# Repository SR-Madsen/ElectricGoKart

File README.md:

# Electric Go-Kart
Repository for 1st semester project of the Master in Electronics at the University of Southern Denmark relating to controlling a Permanent-Magnet Synchronous Motor for an electric go-kart.

## Purpose
The repository contains KiCad files and programming files from Vivado and the Xilinx SDK used for designing a three-phase inverter with a Zybo Zynq-7010 processing unit as core. As described within the repository, a system already exists that the inverter must fit within.

## Overview

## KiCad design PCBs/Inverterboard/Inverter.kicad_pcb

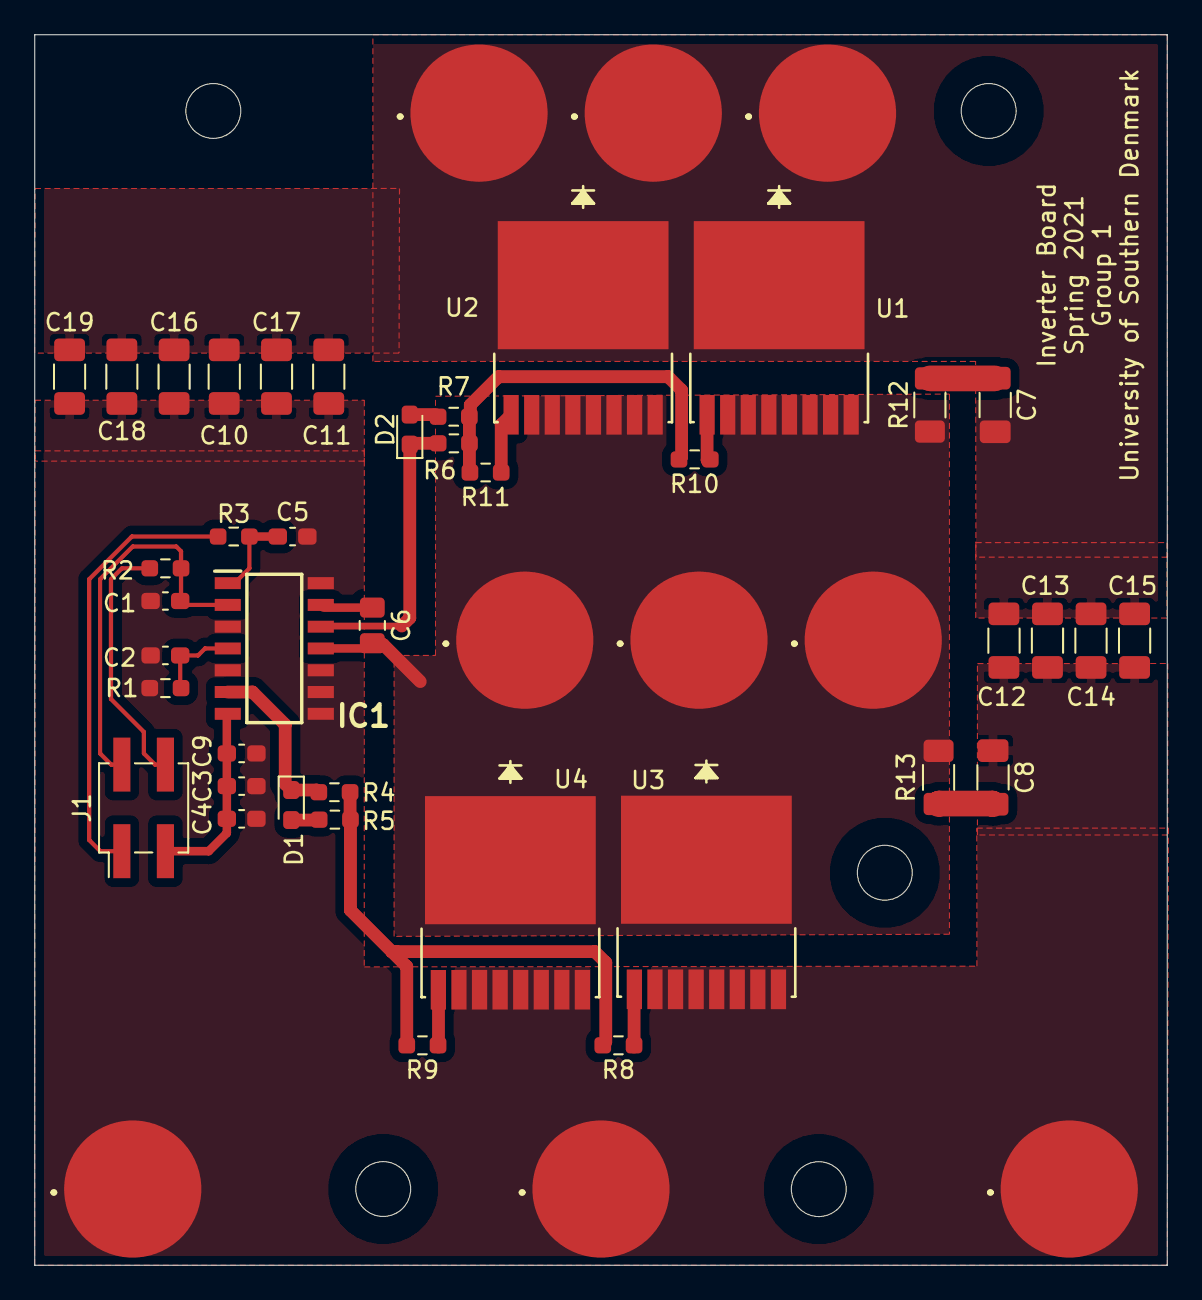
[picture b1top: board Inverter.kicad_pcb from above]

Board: 2 copper layers, 66.0 x 71.8 mm, 49 parts (0 on the bottom side), 22 nets.

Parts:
C1, C9: 1n; C_0603_1608Metric_Pad1.08x0.95mm_HandSolder
C2, C4: 100n; C_0603_1608Metric_Pad1.08x0.95mm_HandSolder
C3: 1µ; C_0603_1608Metric_Pad1.08x0.95mm_HandSolder
C5: 100p; C_0603_1608Metric_Pad1.08x0.95mm_HandSolder
C6: 1µ; C_0805_2012Metric_Pad1.18x1.45mm_HandSolder
C7, C8: 33n; C_1206_3216Metric_Pad1.33x1.80mm_HandSolder
C10, C11, C16, C17, C18, C19: 4.7µ; C_1206_3216Metric_Pad1.33x1.80mm_HandSolder
C12: 1µ; C_1206_3216Metric_Pad1.33x1.80mm_HandSolder
C13: 100n; C_1206_3216Metric_Pad1.33x1.80mm_HandSolder
C14: 10n; C_1206_3216Metric_Pad1.33x1.80mm_HandSolder
C15: 1n; C_1206_3216Metric_Pad1.33x1.80mm_HandSolder
D1, D2: D; D_0603_1608Metric_Pad1.05x0.95mm_HandSolder
IC1: L6494LDTR
J1: Conn_02x02_Odd_Even; PinHeader_2x02_P2.54mm_Vertical_SMD
R1: 1k; R_0603_1608Metric_Pad0.98x0.95mm_HandSolder
R2: 10k; R_0603_1608Metric_Pad0.98x0.95mm_HandSolder
R3: 2k; R_0603_1608Metric_Pad0.98x0.95mm_HandSolder
R4, R6: 22; R_0603_1608Metric_Pad0.98x0.95mm_HandSolder
R5, R7: 0; R_0603_1608Metric_Pad0.98x0.95mm_HandSolder
R8, R9, R10, R11: 3.3; R_0603_1608Metric_Pad0.98x0.95mm_HandSolder
R12, R13: 1; R_1206_3216Metric_Pad1.30x1.75mm_HandSolder
U1, U2, U3, U4: PG-HSOF-8-1_INF; IPT015N10N5ATMA1
U**: 7466203R
U**#2, U**#3, U**#4, U**#5, U**#6, U**#7, U**#8, U**#9: 7466203R

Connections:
+5V: J1.4, R2.1
+12V: C3.1, C4.2, C9.1, IC1.7, J1.3
+BATT: C7.2, C10.1, C11.1, C12.1, C13.1, C14.1, C15.1, C16.1, C17.1, C18.1, C19.1, U1.9, U2.9, U**#7.1, U**#8.1, U**#9.1
Enable: C1.1, IC1.2, J1.2, R2.2
GND: C1.2, C2.2, C3.2, C4.1, C5.2, C8.1, C9.2, C10.2, C11.2, C12.2, C13.2, C14.2, C15.2, C16.2, C17.2, C18.2, C19.2, IC1.3, IC1.5, IC1.8, IC1.9, IC1.10, IC1.14, R1.2, U3.2, U3.3, U3.4, U3.5, U3.6, U3.7, U3.8, U4.2, U4.3, U4.4, U4.5, U4.6, U4.7, U4.8, U**.1, U**#2.1, U**#3.1
unnamed: C2.1, IC1.4, R1.1
unnamed: C5.1, IC1.1, R3.1
unnamed: C6.1, IC1.13
unnamed: C7.1, R12.2
unnamed: C8.2, R13.1
unnamed: D1.1, IC1.6, R4.2
unnamed: D1.2, R5.2
unnamed: D2.1, IC1.12, R6.2
unnamed: D2.2, R7.2
unnamed: R4.1, R5.1, R8.2, R9.2
unnamed: R8.1, U3.1
unnamed: R9.1, U4.1
unnamed: R10.1, U1.1
unnamed: R6.1, R7.1, R10.2, R11.2
unnamed: R11.1, U2.1
PHASE: C6.2, IC1.11, R12.1, R13.2, U1.2, U1.3, U1.4, U1.5, U1.6, U1.7, U1.8, U2.2, U2.3, U2.4, U2.5, U2.6, U2.7, U2.8, U3.9, U4.9, U**#4.1, U**#5.1, U**#6.1
PWM: J1.1, R3.2

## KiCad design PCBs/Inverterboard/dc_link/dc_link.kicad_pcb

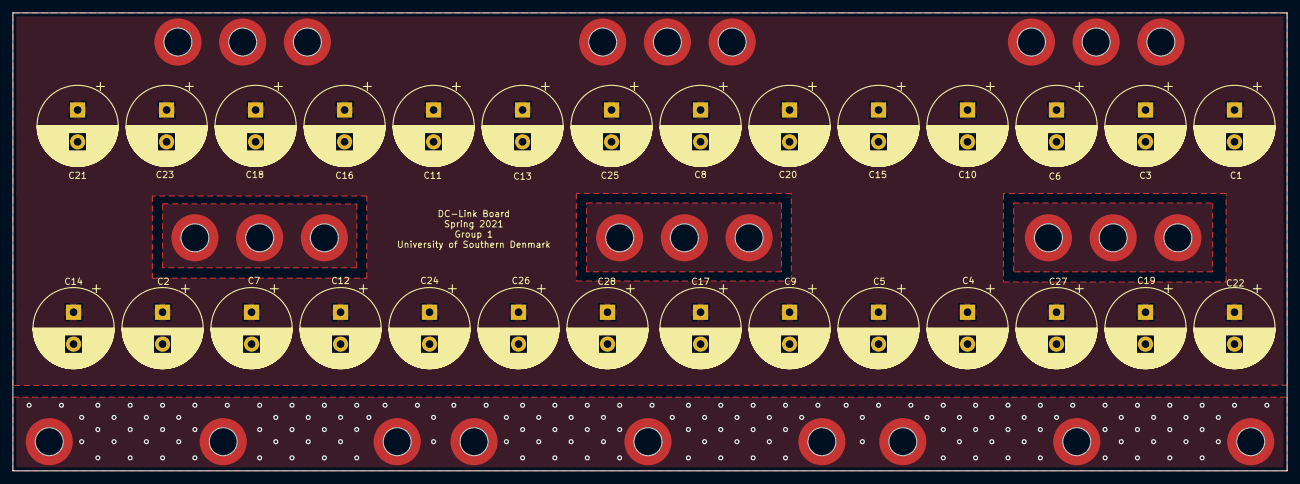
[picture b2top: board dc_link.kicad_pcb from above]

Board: 2 copper layers, 200.0 x 71.9 mm, 28 parts (0 on the bottom side), 2 nets.

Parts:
C1, C2, C3, C4, C5, C6, C7, C8, C9, C10, C11, C12, C13, C14, C15, C16, C17, C18, C19, C20, C21, C22, C23, C24, C25, C26, C27, C28: CP; CP_Radial_D12.5mm_P5.00mm

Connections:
+BATT: C1.1, C2.1, C3.1, C4.1, C5.1, C6.1, C7.1, C8.1, C9.1, C10.1, C11.1, C12.1, C13.1, C14.1, C15.1, C16.1, C17.1, C18.1, C19.1, C20.1, C21.1, C22.1, C23.1, C24.1, C25.1, C26.1, C27.1, C28.1
GND: C1.2, C2.2, C3.2, C4.2, C5.2, C6.2, C7.2, C8.2, C9.2, C10.2, C11.2, C12.2, C13.2, C14.2, C15.2, C16.2, C17.2, C18.2, C19.2, C20.2, C21.2, C22.2, C23.2, C24.2, C25.2, C26.2, C27.2, C28.2

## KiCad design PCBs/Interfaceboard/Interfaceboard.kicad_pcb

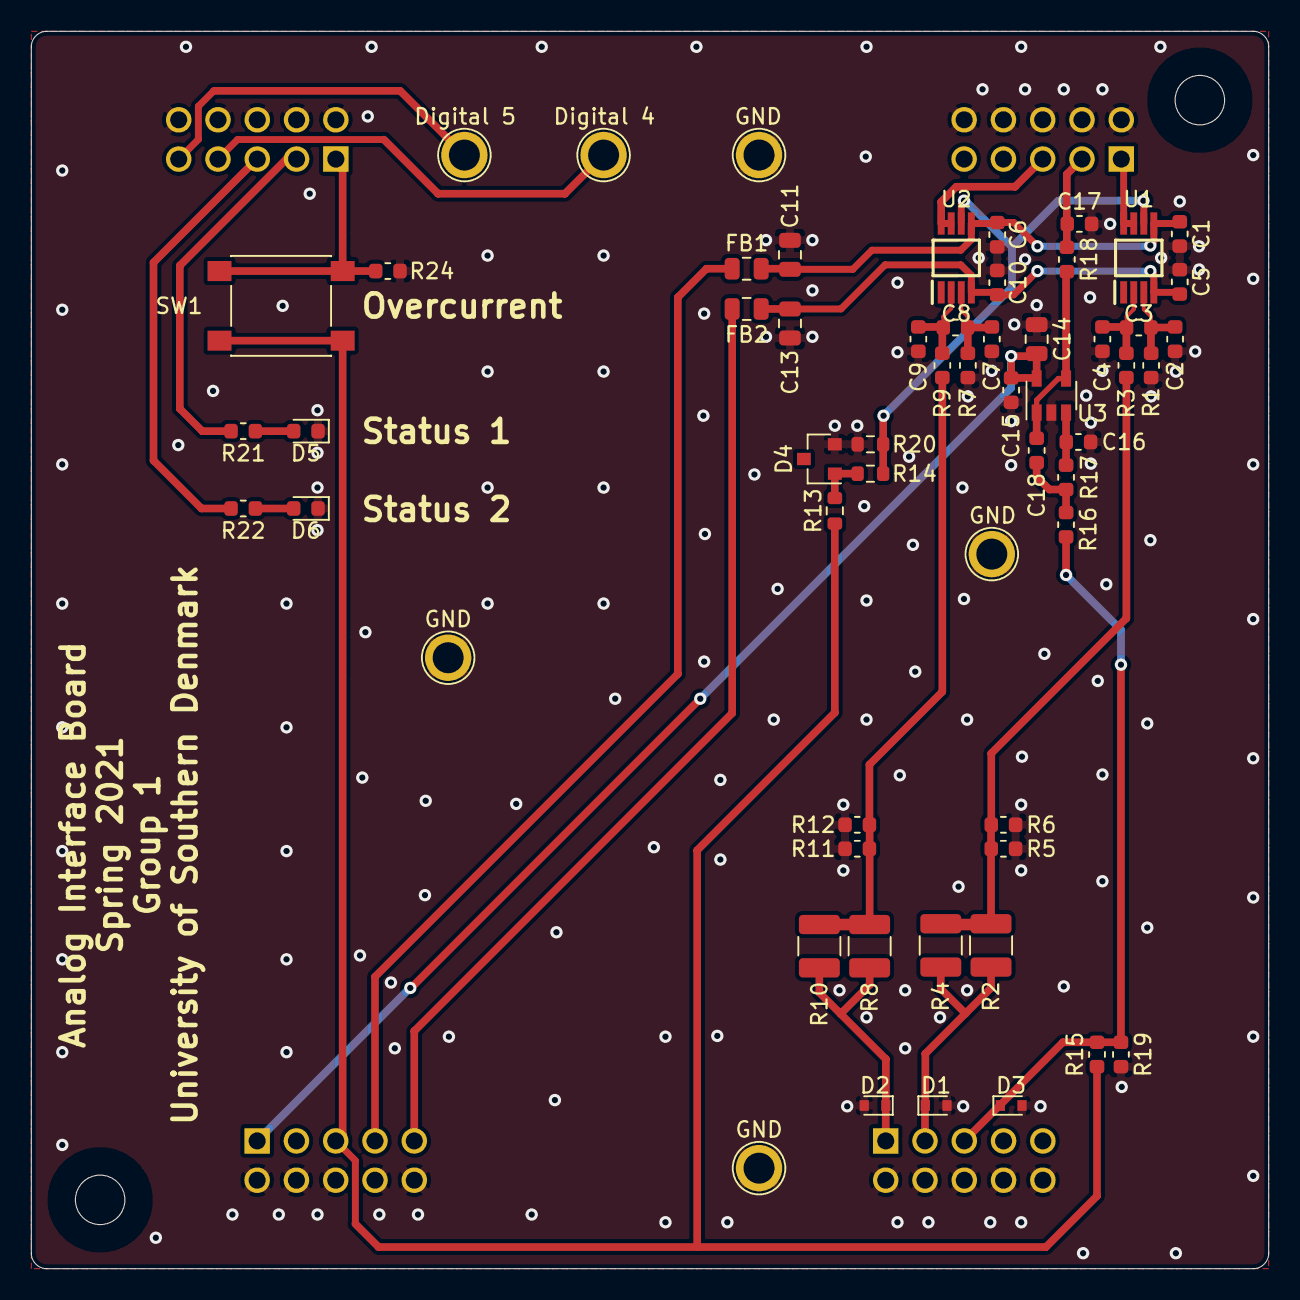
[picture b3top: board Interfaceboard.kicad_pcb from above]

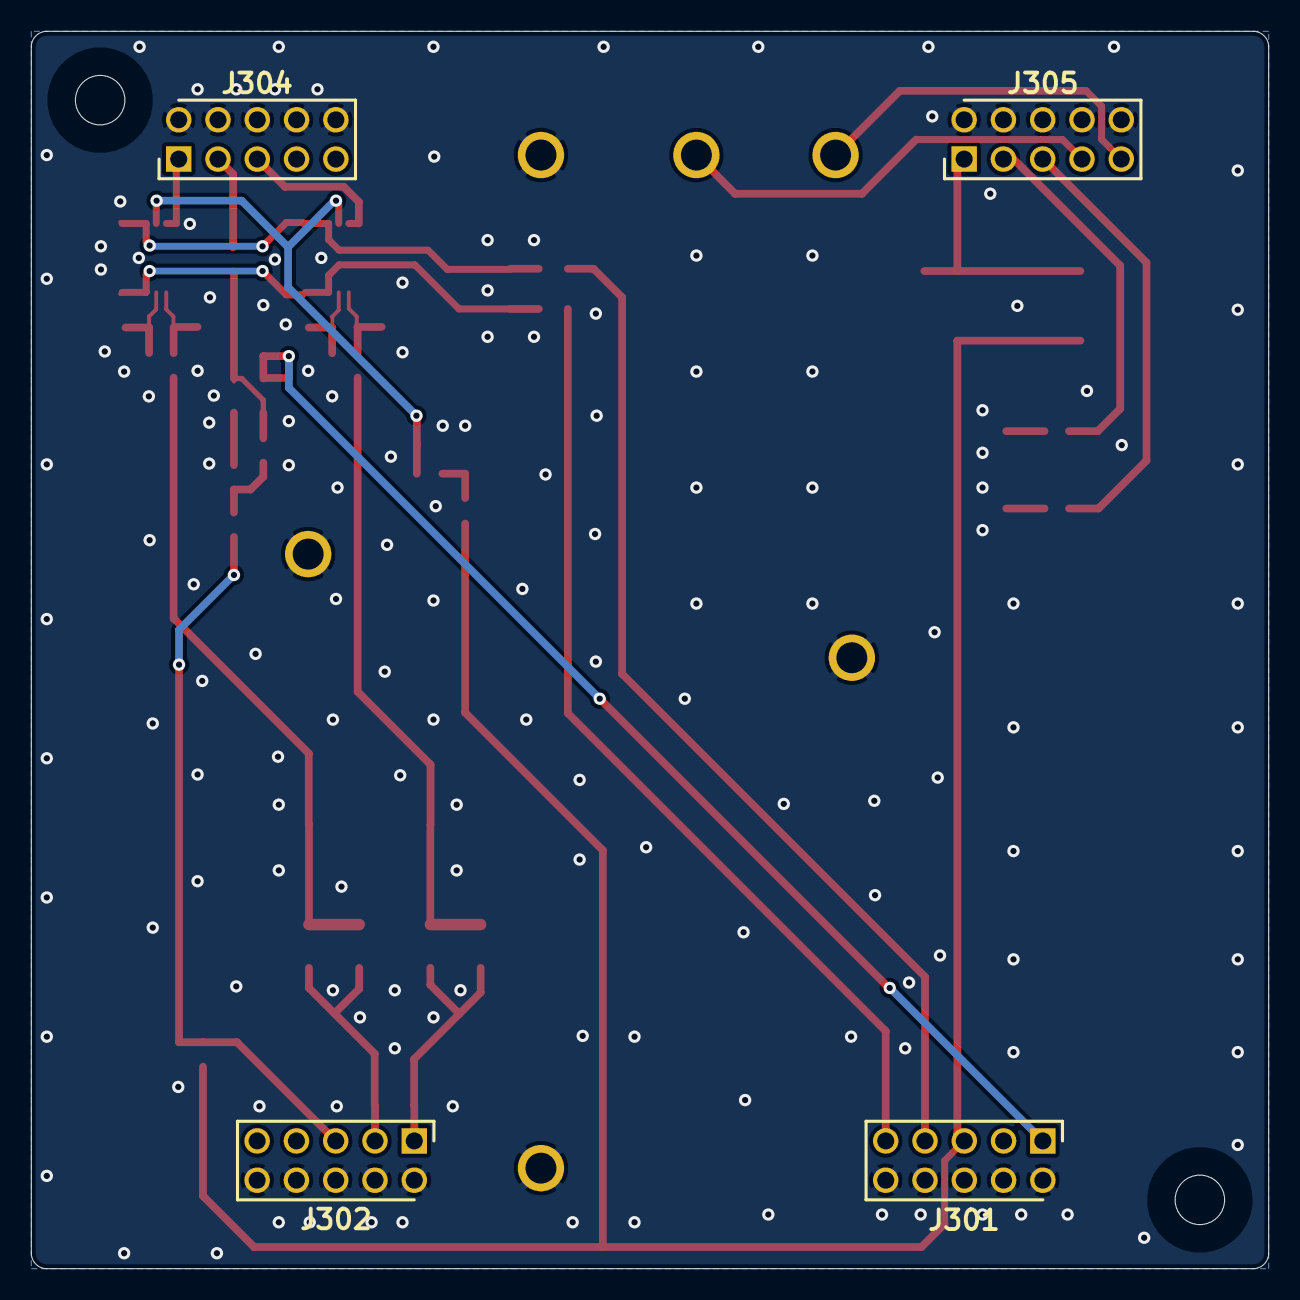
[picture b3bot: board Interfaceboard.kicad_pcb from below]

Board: 2 copper layers, 80.0 x 80.0 mm, 64 parts (4 on the bottom side), 31 nets.

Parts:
C1, C5, C6, C10, C15: 100n; C_0603_1608Metric
C2, C4, C7, C9: 100p; C_0603_1608Metric
C3, C8: 1n; C_0603_1608Metric
C11, C13, C14: 10µ; C_0805_2012Metric
C16: 30n; C_0603_1608Metric
C17: 33n; C_0603_1608Metric
C18: 56n; C_0603_1608Metric
D1, D2: 5 V; D_SOD-523
D3: 3.3 V; D_SOD-523
D4: LM4041CFTA; LM4041
D5: 150060SS75000; LED_0603_1608Metric
D6: 150060VS75000; LED_0603_1608Metric
FB1, FB2: 400 mA, 1k5; L_0805_2012Metric
H1, H2: M3 Mount; MountingHole_3.2mm_M3
J301, J302, J304, J305: TSW-105-07-T-D
R1, R3, R7, R9: 20k; R_0603_1608Metric
R2, R8: 54.9; R_1210_3225Metric
R4, R10: 56; R_1210_3225Metric
R5, R11: 3.09; R_0603_1608Metric
R6, R12: DNP; R_0603_1608Metric
R13: 5.1k; R_0603_1608Metric
R14: 1.43k; R_0603_1608Metric
R15: 11.5k; R_0603_1608Metric
R16, R17: 7.5k; R_0603_1608Metric
R18: 147; R_0603_1608Metric
R19, R24: 10k; R_0603_1608Metric
R20: 1k; R_0603_1608Metric
R21, R22: 270; R_0603_1608Metric
SW1: PTS645; SW_SPST_PTS645
TP4, TP5, TP6, TP7, TP8, TP9: TestPoint; TestPoint_Plated_Hole_D2.0mm
U1, U2: AD8420ARMZ
U3: MCP6L01x-xOT; SOT-23-5

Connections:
+3V3_Ref: J301.5, R13.2, R15.1, SW1.1
+5V: C14.1, C15.1, J301.1, U3.5
+15V: FB1.1, J301.7
-15V: FB2.2, J301.9
/Buttons/Dig1: J305.1, R24.1, SW1.2
/Buttons/Dig2: J305.3, R21.2
/Buttons/Dig3: J305.5, R22.2
/Buttons/Dig4: J305.7, TP8.1
/Buttons/Dig5: J305.9, TP9.1
/Connectors/ADC1: J304.1, U1.7, U1.8
/Connectors/ADC3: C17.1, J304.3, R18.1
/Connectors/ADC4: J304.5, U2.7, U2.8
/Connectors/Torque_Meas: D3.1, J302.5, R15.2, R16.2, R19.1
/Currents/0V5: R14.1, R20.2, U1.6, U2.6
/Currents/+15V_Filt: C1.1, C6.1, C11.1, FB1.2, U1.5, U2.5
/Currents/-15V_Filt: C5.1, C10.1, C13.2, FB2.1, U1.4, U2.4
/Currents/Phase1_In: D2.1, J302.1, R8.2, R10.2
/Currents/Phase2_In: D1.1, J302.3, R2.2, R4.2
GND: C1.2, C2.1, C4.2, C5.2, C6.2, C7.1, C9.2, C10.2, C11.2, C13.1, C14.2, C15.2, C16.2, C17.2, D1.2, D2.2, D3.2, D4.2, D5.1, D6.1, J301.2, J301.4, J301.6, J301.8, J301.10, J302.2, J302.4, J302.6, J302.8, J302.10, J304.2, J304.4, J304.6, J304.8, J304.10, J305.2, J305.4, J305.6, J305.8, J305.10, R1.2, R5.1, R6.1, R7.2, R11.1, R12.1, R19.2, R20.1, R24.2, TP4.1, TP5.1, TP6.1, TP7.1, U3.2
unnamed: C2.2, C3.1, R1.1, U1.3
unnamed: C3.2, C4.1, R3.1, U1.2
unnamed: C7.2, C8.1, R7.1, U2.3
unnamed: C8.2, C9.1, R9.1, U2.2
unnamed: C16.1, R17.1, U3.3
unnamed: C18.1, R18.2, U3.1, U3.4
unnamed: C18.2, R16.1, R17.2
unnamed: D4.1, R13.1, R14.2
unnamed: D5.2, R21.1
unnamed: D6.2, R22.1
unnamed: R2.1, R3.2, R4.1, R5.2, R6.2
unnamed: R8.1, R9.2, R10.1, R11.2, R12.2

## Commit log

2021-02-16 Initial commit of datasheets, KiCad project, and overview.
2021-02-17 Added newest datasheets Rakesh put up. Added some links for software design. Minor changes to draw.io file.
2021-02-18 Added KiCad Libraries for this project. Added 35 pin connector to schematic.
2021-02-19 Split into two PCBs, made sub-sheets for most. Added connectors and comments.
2021-02-20 Added multiple connectors, still lacking a few. Started work on measurement circuits for interface board.
2021-02-23 Added most circuits from Interface schematic provided by Rakesh. Lacks a few connectors, transistors, and optocouplers. Needs connections for Zybo. Awaiting feedback from meeting with Rakesh.
2021-02-23 Added Interface Board schematics
    * Added KiCad Libraries for this project. Added 35 pin connector to schematic.
    * Split into two PCBs, made sub-sheets for most. Added connectors and comments.
    * Added multiple connectors, still lacking a few. Started work on measurement circuits for interface board.
    * Added most circuits from Interface schematic provided by Rakesh. Lacks a few connectors, transistors, and optocouplers. Needs connections for Zybo. Awaiting feedback from meeting with Rakesh.
2021-03-04 Removed interface board, added analog interface board.
2021-03-08 Added analog board hierarchial sheets. Started work on connectors, supply, and in amp for phase current measurements.
2021-03-10 Finished schematics for analog interface board. Ready for review and then PCB design.
2021-03-13 Added test points and final associated footprints. Made outline for PCB.
2021-03-15 Made changes to resistor sizes and footprints. Placed switches on PCB, ready for the rest.
2021-03-15 Minor changes to schematics, removed test points, placed a few components on PCB.
2021-03-16 Removed some buttons and added LEDs. Finished placing the components on the PCB.
2021-03-16 Minor cosmetic and performance changes. PCB basically finished, needs more eyes for review.
2021-03-17 Changed M2 to M3 hole. Vias are free.
2021-03-17 Swapped some ADC channels for the signals to ensure that simultaneous conversion is possible.
2021-03-22 Merge of 'Analog Board' into main (#2)
    * Added analog board schematics and finished PCB.
    * Added a few documentation files.
2021-03-23 Added Vivado project and PWM Generator + Encoder driver IPs. Encoder driver still unfinished.
2021-03-24 Fully-tested and functional PWM IP added. Encoder module still needs simulation and further polishing.
2021-03-25 Tested and fixed Encoder driver, added both IPs to main project.
2021-03-25 Made final changes to PWM generator and Encoder driver IPs.
2021-03-26 Made final fixes to IP cores, ran implementation and bitstream of module. Added GPIO IPs and assigned pins.
2021-03-29 Fixed asynchronous reset error for IPs and optimized a bit. Now fully functional.
2021-04-03 Merge of VHDL Modules (#3)
    * Added Vivado project.
    * Created PWM Generator and Encoder Driver IPs, which along with XADC, PS, and GPIO are used in the block diagram.
    * Assigned all pins and created constraints file for timing, bitstream generated.
2021-04-03 Added progress for inverterboard and DC-link by the Jackobs. Merged libraries, added 3D models for swag factor.
2021-04-04 Added and made changes to software overview. Added PS Interrupt from XADC.
2021-04-06 Merged PCB with changes from Jakob. Added FOC overview.
2021-04-06 Connected MOSFET sources
2021-04-06 Changed mini-fits to pin headers
2021-04-08 Added mini-fit to enable and pwm signals
2021-04-13 Changed ceramic DC-link cap footprint size
2021-04-13 Made minor changes to PCB to accommodate review feedback.
2021-04-16 Last fixes after PCB review
2021-04-16 Created gerber files
2021-04-16 Something that apparently didn't get pushed before
2021-04-16 Correct gerber
2021-04-16 Now it is correct gerber files
2021-04-16 change in gate resistor
2021-04-16 Made final Gerber files for all boards.
2021-04-19 Changed Inverter holes so they're good for aluminium. New Gerbers.
2021-04-20 Plecs model with thermal models
2021-04-27 Added SDK project with driver for AXI Interface modules. Lacks testing and possibly merging functions.
2021-04-29 Added XADC driver with interrupt controller functionality, as well as some test code for main.
2021-05-02 Added GPIO driver, made minor changes to AXI Interface driver.
2021-05-04 Wrote programs for testing of driver functionality.
2021-05-06 Made minor changes to Vivado project and AXI Interface, GPIO, and XADC drivers. Tests completed succesfully for all three.
2021-05-06 Merge of updated code and project from testing (#4)
    Added updated Vivado project and drivers after successful testing.
2021-05-06 Added files for sensor task, started work on it.
2021-05-10 Wrapped up sensor task. Working on state machine task and general structure.
2021-05-11 Added park-clarke and pi-controller software
2021-05-11 Almost finished state machine and initialization. Added enable/disable for VHDL components.
2021-05-11 Merge of Sensor Task and State Machine (#5)
    * Added Sensor Task, State Machine, XADC interrupt, general setup and initialization.
    * Added files for structs and general program structure.
    * Added enable/disable for VHDL components.
2021-05-11 Added PI controller and Clarke/Park transformation code. Added FOC minus SVM. Ready for testing of analog board.
2021-05-12 Added Space Vector Modulation, started work on communication task.
2021-05-13 Added more overview. Wrapped up UART set and get task. Fixed minor FOC errors.
2021-05-13 Field-Oriented Control and UART Tasks (#6)
    * Added PI controller and Clarke/Park transformation code. Added Field-Oriented Control. All tested on Zybo with analog board.
    * Added UART communication task to get and set values.
    * Added more overview in form of draw.io drawings.
2021-05-14 Rebuilt program, made very minor changes to UART and some functions.
2021-05-14 Forgot to push metadata.
2021-05-23 Made changes to some defines for analog values. Made HAL folder for structure.
2021-05-24 Cleaned up repo, added fresh simulations.
2021-05-24 Added ZIP file of folders.
2021-05-26 Renamed zip file and added report.
2021-06-06 Added oscillograms and data from tests.
